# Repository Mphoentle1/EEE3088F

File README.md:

# EEE3088F
DoA project

This project involves the design and implementation of a high-precision acoustic sensor capable of determining the Direction of Arrival (DoA) of a specific 2000 Hz beacon. The system integrates custom analog front-end hardware with a high-performance STM32F429ZGT6 microcontroller to process signals in real-time under strict latency constraints.

Technical Specifications

Target Frequency: 2000 Hz 
Sampling Rate: 20,000 Hz (5x oversampling for phase accuracy) 
Microphone Spacing: 50 mm
Supply Voltage: 3.3V DC (Strictly compliant with Automated Testing Rig) 
Communication: I2C Slave (Address: 0x42) 
Latency Ceiling: < 50ms from trigger to DoA result 

System Architecture

Analog Front-End
The signal chain uses a Zilltek ZTS6618 top-ported MEMS microphone for superior assembly reliability. The analog path includes:
AC Coupling: Blocks microphone DC offset.Active 
Bandpass Filter: A Multiple Feedback (MFB) topology using the AD8605 rail-to-rail op-amp, providing ~40dB of gain.
DC Biasing: Centering the signal at 1.65V for unipolar ADC sampling.
Digital ProcessingADC Acquisition: High-speed sampling triggered by the Rig state-machine.
DSP Algorithm: Cross-correlation (CCF) performed on the STM32's hardware Floating Point Unit (FPU) to calculate the time-of-flight difference between the microphone pair.
Register Interface: Results are reported via 32-bit IEEE 754 float registers.

📂 Repository Structure

/Hardware: KiCad PCB files, LTspice simulations, and Bill of Materials (BOM).
/Firmware: STM32CubeIDE project (C code), including CMSIS-DSP implementation.
/instruction_sheets: M1 Technical Contract and Physics Baseline proofs.

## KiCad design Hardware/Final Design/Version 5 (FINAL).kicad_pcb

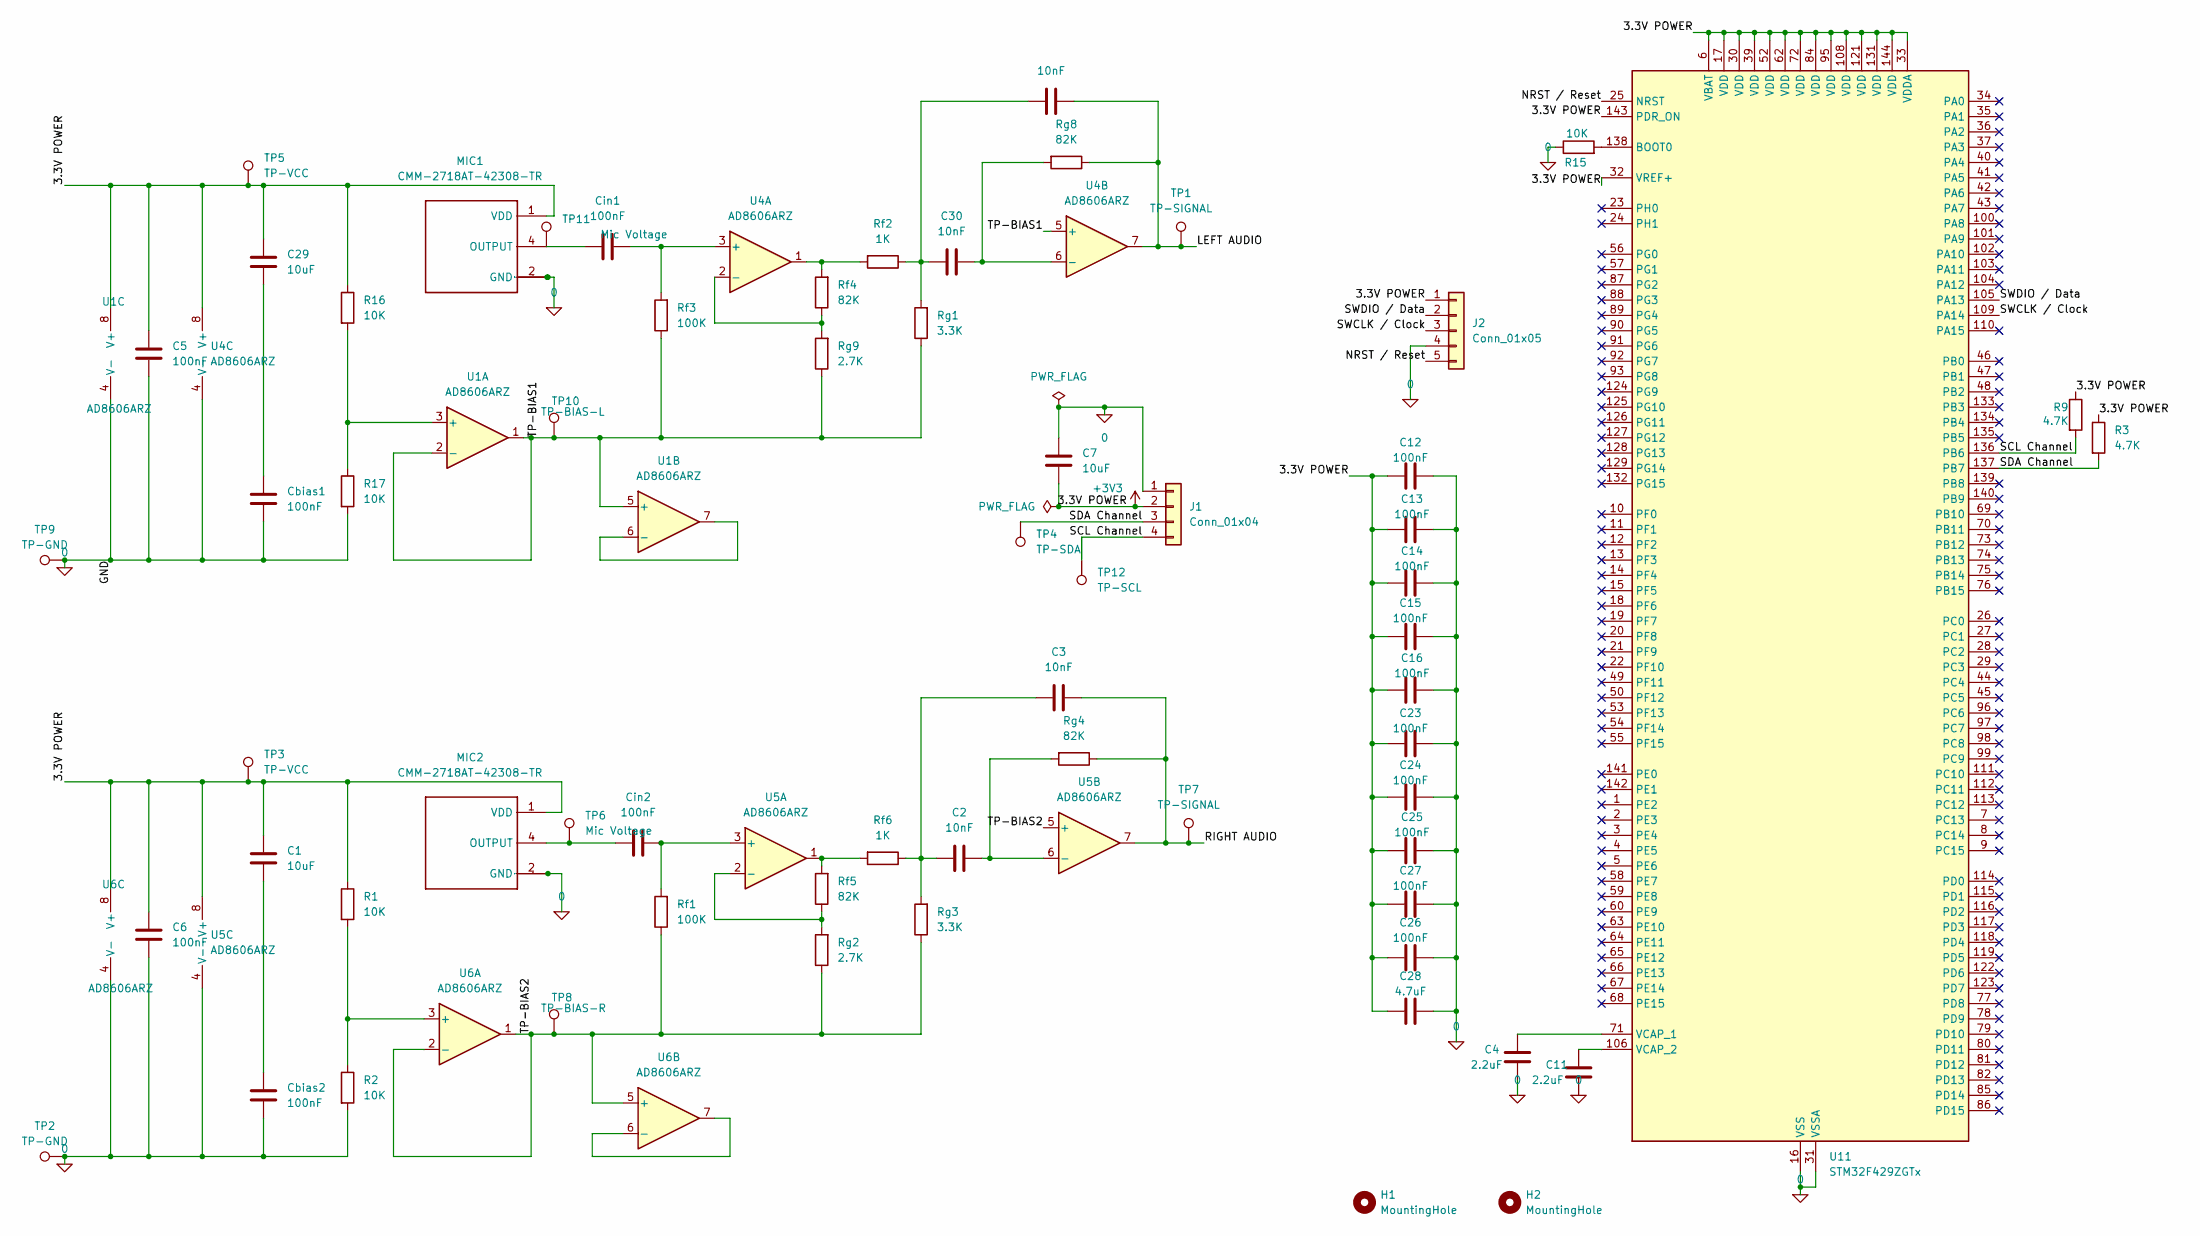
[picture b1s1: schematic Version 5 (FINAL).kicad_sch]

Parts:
C1, C7, C29: 10uF; C0805 (CAPACITOR); LCSC C1713
C2, C3, C30, C31: 10nF; C0805 (CAPACITOR); LCSC C24666
C4, C11: 2.2uF; C0805 (CAPACITOR); LCSC C1731
C5, C6, C12, C13, C14, C15, C16, C23, C24, C25, C26, C27: 100nF; C0805 (CAPACITOR); LCSC C29926
C28: 4.7uF; C0805 (CAPACITOR); LCSC C1746
Cbias1, Cbias2: 100nF; C0805 (CAPACITOR); LCSC C29926
Cin1, Cin2: 100nF; C0805 (CAPACITOR); LCSC C29926
H1, H2: MountingHole; MountingHole_3.2mm_M3
J1: Conn_01x04; PinHeader_1x04_P2.54mm_Horizontal
J2: Conn_01x05; PinHeader_1x05_P2.54mm_Vertical
MIC1, MIC2: CMM-2718AT-42308-TR; XDCR_CMM-2718AT-42308-TR (MIC); LCSC C3171756
R1, R2, R15, R16, R17: 10K; R0805 (RESISTOR); LCSC C84376
R3, R9: 4.7K; R0805 (RESISTOR); LCSC C17673
Rf1, Rf3: 100K; R0805 (RESISTOR); LCSC C96346
Rf2, Rf6: 1K; R0805 (RESISTOR); LCSC C2904551
Rf4, Rf5: 82K; R0805 (RESISTOR); LCSC C101876
Rg1, Rg3: 3.3K; R0805 (RESISTOR); LCSC C26010
Rg2, Rg9: 2.7K; R0805 (RESISTOR); LCSC C101616
Rg4, Rg8: 82K; R0805 (RESISTOR); LCSC C101876
TP1, TP7: TP-SIGNAL; TestPoint_Pad_2.0x2.0mm
TP2, TP9: TP-GND; TestPoint_Pad_2.5x2.5mm
TP3, TP5: TP-VCC; TestPoint_Pad_2.0x2.0mm
TP4: TP-SDA; TestPoint_Pad_2.0x2.0mm
TP6, TP11: Mic Voltage; TestPoint_Pad_2.0x2.0mm
TP8: TP-BIAS-R; TestPoint_Pad_2.0x2.0mm
TP10: TP-BIAS-L; TestPoint_Pad_2.0x2.0mm
TP12: TP-SCL; TestPoint_Pad_2.0x2.0mm
U1, U4, U5, U6: AD8606ARZ; AD8606ARZ-REEL7 (OPAMP); LCSC C22365308
U11: STM32F429ZGTx; LQFP-144_20x20mm_P0.5mm; LCSC C46525

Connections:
0: C4.1, C5.2, C6.2, C7.2, C11.1, C12.2, C13.1, C14.2, C15.2, C16.2, C23.2, C24.2, C25.2, C26.2, C27.2, C28.2, Cbias1.2, Cbias2.2, J1.1, J2.4, MIC1.2 (GND), MIC1.3 (GND), MIC2.2 (GND), MIC2.3 (GND), R2.2, R15.1, R17.2, TP2.1, TP9.1, U1.4 (V-), U4.4 (V-), U5.4 (V-), U6.4 (V-), U11.16 (VSS), U11.31 (VSSA), U11.38 (VSS), U11.51 (VSS), U11.61 (VSS), U11.83 (VSS), U11.94 (VSS), U11.107 (VSS), U11.120 (VSS), U11.130 (VSS)
+3V3: C1.1, C5.1, C6.1, C7.1, C12.1, C13.2, C14.1, C15.1, C16.1, C23.1, C24.1, C25.1, C26.1, C27.1, C28.1, C29.1, J1.2, J2.1, MIC1.1 (VDD), MIC2.1 (VDD), R1.1, R3.1, R9.1, R16.1, TP3.1, TP5.1, U1.8 (V+), U4.8 (V+), U5.8 (V+), U6.8 (V+), U11.6 (VBAT), U11.17 (VDD), U11.30 (VDD), U11.32 (VREF+), U11.33 (VDDA), U11.39 (VDD), U11.52 (VDD), U11.62 (VDD), U11.72 (VDD), U11.84 (VDD), U11.95 (VDD), U11.108 (VDD), U11.121 (VDD), U11.131 (VDD), U11.143 (PDR_ON), U11.144 (VDD)
/LEFT AUDIO: C31.2, Rg8.1, TP1.1, U4.7
/NRST / Reset: J2.5, U11.25 (NRST)
/RIGHT AUDIO: C3.2, Rg4.1, TP7.1, U5.7
/SCL Channel: J1.4, R9.2, TP12.1, U11.136 (PB6)
/SDA Channel: J1.3, R3.2, TP4.1, U11.137 (PB7)
/SWCLK / Clock: J2.3, U11.109 (PA14)
/SWDIO / Data: J2.2, U11.105 (PA13)
/TP-BIAS1: Rf3.1, Rg1.1, Rg9.1, TP10.1, U1.1, U1.2 (-), U1.5 (+), U4.5 (+)
/TP-BIAS2: Rf1.1, Rg2.1, Rg3.1, TP8.1, U5.5 (+), U6.1, U6.2 (-), U6.5 (+)
unnamed: C1.2, Cbias2.1
unnamed: C2.1, C3.1, Rf6.1, Rg3.2
unnamed: C29.2, Cbias1.1
unnamed: C30.1, C31.1, Rf2.1, Rg1.2
unnamed: Cin1.1, MIC1.4 (OUTPUT), TP11.1
unnamed: Cin2.1, MIC2.4 (OUTPUT), TP6.1
unnamed: Rf2.2, Rf4.2, U4.1
unnamed: Rf5.2, Rf6.2, U5.1
unnamed: R16.2, R17.1, U1.3 (+)
unnamed: U1.6 (-), U1.7
unnamed: Cin1.2, Rf3.2, U4.3 (+)
unnamed: Rf4.1, Rg9.2, U4.2 (-)
unnamed: C30.2, Rg8.2, U4.6 (-)
unnamed: Cin2.2, Rf1.2, U5.3 (+)
unnamed: Rf5.1, Rg2.2, U5.2 (-)
unnamed: C2.2, Rg4.2, U5.6 (-)
unnamed: R1.2, R2.1, U6.3 (+)
unnamed: U6.6 (-), U6.7
unnamed: R15.2, U11.138 (BOOT0)
unnamed: C4.2, U11.71 (VCAP_1)
unnamed: C11.2, U11.106 (VCAP_2)

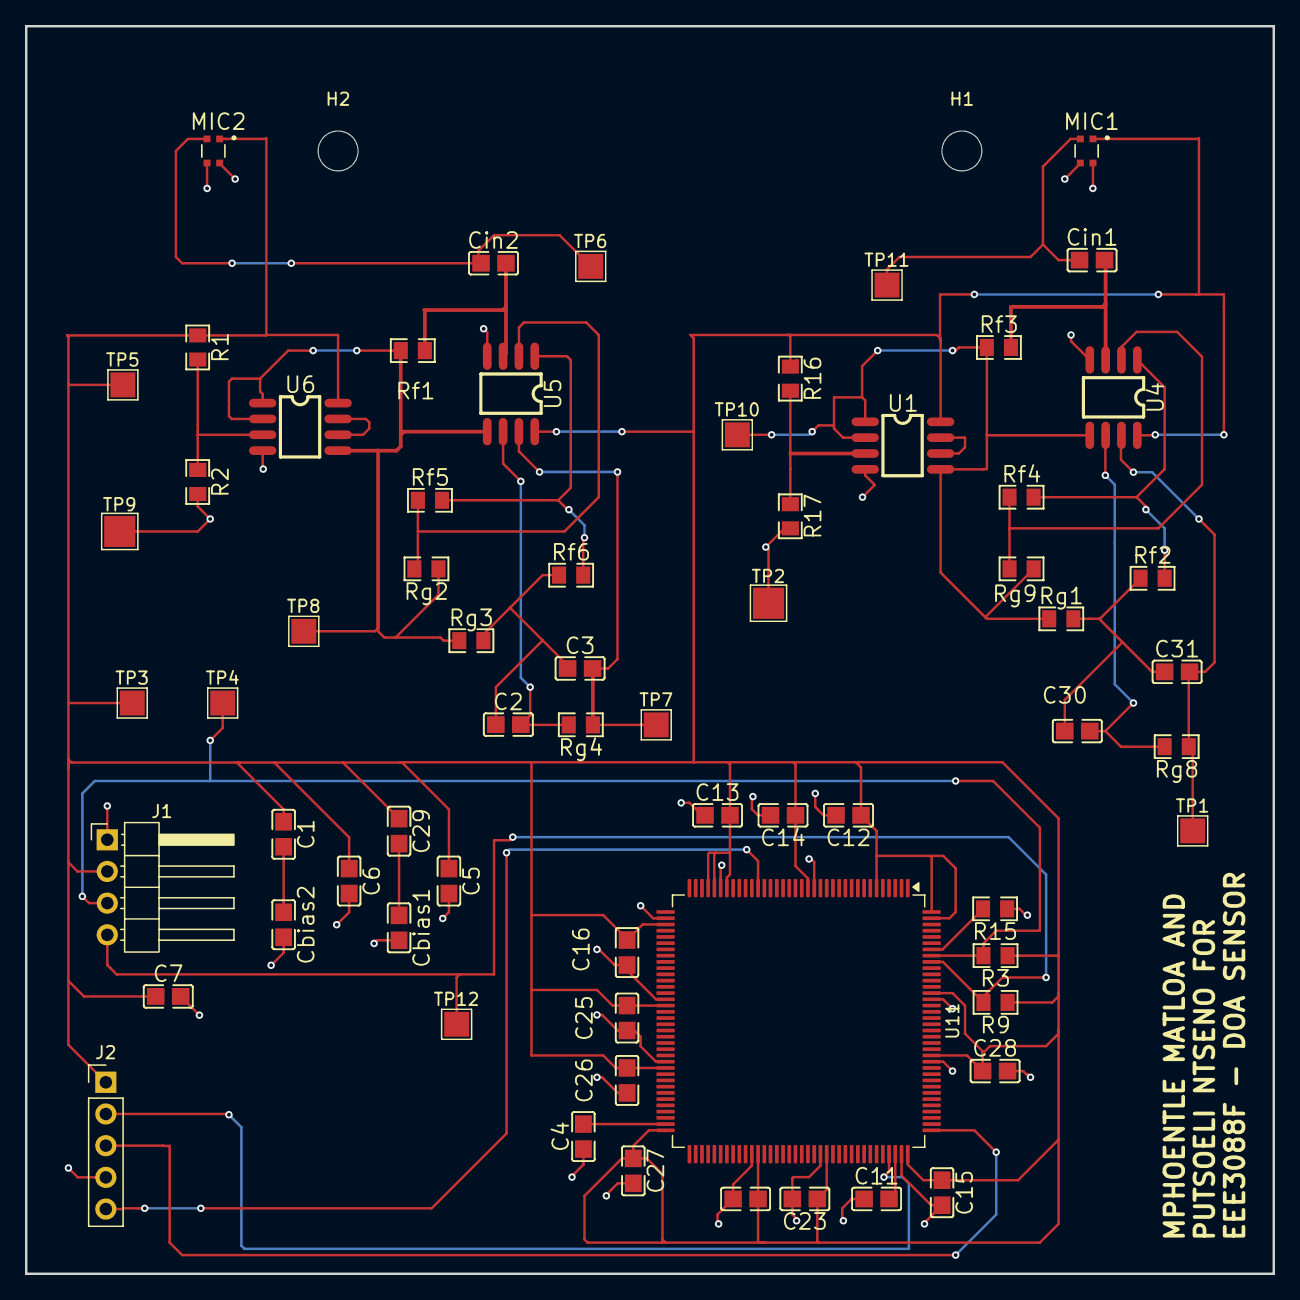
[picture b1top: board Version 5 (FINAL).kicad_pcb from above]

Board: 2 copper layers, 100.0 x 100.0 mm, 68 parts (0 on the bottom side), 32 nets.

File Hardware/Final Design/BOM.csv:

Comment,Designator,Footprint,LCSC,Quantity
100K,"Rf1,Rf3",R0805 (RESISTOR),C149504,2
100nF,"C12,C13,C14,C15,C16,C23,C24,C25,C26,C27,C5,C6,Cbias1,Cbias2,Cin1,Cin2",C0805 (CAPACITOR),C28233,16
10K,"R1,R15,R16,R17,R2",R0805 (RESISTOR),C17414,5
10nF,"C2,C3,C30,C31",C0805 (CAPACITOR),C1710,4
10uF,"C1,C29,C7",C0805 (CAPACITOR),C15850,3
1K,"Rf2,Rf6",R0805 (RESISTOR),C17513,2
2.2uF,"C11,C4",C0805 (CAPACITOR),C377773,2
2.7K,"Rg2,Rg9",R0805 (RESISTOR),C17530,2
3.3K,"Rg1,Rg3",R0805 (RESISTOR),C26010,2
4.7K,"R3,R9",R0805 (RESISTOR),C17673,2
4.7uF,C28,C0805 (CAPACITOR),C1779,1
82K,"Rf4,Rf5,Rg4,Rg8",R0805 (RESISTOR),C23254,4
AD8606ARZ,"U1,U4,U5,U6",AD8606ARZ-REEL7 (OPAMP),C22365308,4
CMM-2718AT-42308-TR,"MIC1,MIC2",XDCR_CMM-2718AT-42308-TR (MIC),C3171756,2
STM32F429ZGTx,U11,LQFP-144_20x20mm_P0.5mm,C46525,1

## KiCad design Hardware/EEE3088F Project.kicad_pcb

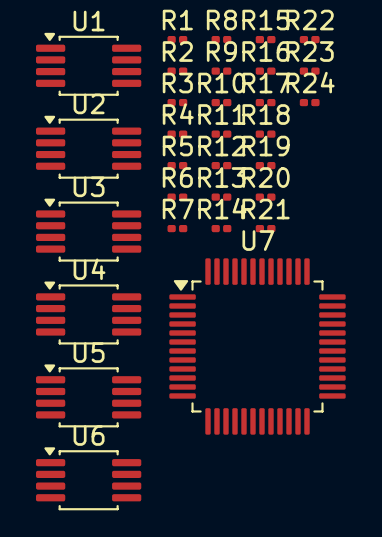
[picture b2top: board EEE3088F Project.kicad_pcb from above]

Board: 2 copper layers, 31 parts (0 on the bottom side), 24 nets, no tracks yet.

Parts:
R1, R2, R3, R4, R6, R7, R9, R10, R12, R14, R16, R17, R18, R20, R23: 10K; R_0201_0603Metric
R5, R8, R11, R13, R15, R19, R24: 100K; R_0201_0603Metric
R21, R22: 100; R_0201_0603Metric
U1, U2, U3, U4, U5, U6: OP1177ARM; MSOP-8_3x3mm_P0.65mm
U7: STM32F051C6Tx; LQFP-48_7x7mm_P0.5mm

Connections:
0: R2.2, R4.2, R23.1, U1.4 (V-), U2.4 (V-), U3.4 (V-), U4.4 (V-), U5.4 (V-), U6.4 (V-), U7.8 (VSSA), U7.23 (VSS), U7.47 (VSS)
+3.3V: R1.1, R3.1, R24.2, U1.7 (V+), U2.7 (V+), U3.7 (V+), U4.7 (V+), U5.7 (V+), U7.1 (VBAT), U7.9 (VDDA), U7.24 (VDD), U7.48 (VDD)
/LEFT AUDIO: R5.1, R22.2, U6.6
/RIGHT AUDIO: R19.1, R21.2, U5.6
/SDA Channel: R24.1, U7.43 (PB7)
unnamed: R1.2, R2.1, R9.2
unnamed: R3.2, R4.1, R10.2
unnamed: R11.1, R18.1, U2.6
unnamed: R15.1, R17.1, U1.6
unnamed: R9.1, U1.3 (+)
unnamed: R15.2, R16.1, U1.2 (-)
unnamed: R10.1, U2.3 (+)
unnamed: R11.2, R12.1, U2.2 (-)
unnamed: R17.2, U3.3 (+)
unnamed: R13.2, R14.1, U3.2 (-)
unnamed: R18.2, U4.3 (+)
unnamed: R7.1, R8.2, U4.2 (-)
unnamed: R13.1, U3.6, U5.3 (+)
unnamed: R19.2, R20.1, U5.2 (-)
unnamed: R8.1, U4.6, U6.3 (+)
unnamed: R5.2, R6.1, U6.2 (-)
unnamed: R23.2, U7.44 (BOOT0)
unnamed: R21.1, U7.10 (PA0)
unnamed: R22.1, U7.14 (PA4)

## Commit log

2026-03-12 Create Hardware
2026-03-12 Create firmware
2026-03-12 Create Instruction_sheets
2026-03-12 Rename Instruction_sheet to Instruction_sheets
2026-03-13 Delete Hardware
    This was a blank text file not a sub directory
2026-03-13 Create README.md
    Created a hardware folder to put the schematics
2026-03-13 Kicad files upload
2026-03-13 Create Opamp Model Directory
2026-03-13 Create Opamp Model File
2026-03-13 Create opamp.lib
    Creating a model for an opamp for Kicad
2026-03-13 Create Firmware Directory
2026-03-13 Uploaded a README file for the firmware
2026-03-15 Upload updated files
